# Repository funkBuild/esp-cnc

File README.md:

TODO
- position callback called on a timer. Motion handlers register with it for each axis
- Convert stepper to use position as mm instead of steps

- Brake outputs for each axis
- spindle speed variation. M138 / M139
  https://www.haascnc.com/service/codes-settings.type=mcode.machine=mill.value=M138.html

Haas - 
4th axis - M11 unclamp, M10 clamp
5th axis - M13 unclamp, M12 clamp

- Properly calculate feed rate on 3 axis (GRBL is wrong??)
- Calculate 5 axis feed rate using distance to axis of rotation
- Support inverse time feed rate

http://linuxcnc.org/docs/devel/html/motion/5-axis-kinematics.html
http://linuxcnc.org/docs/html/gcode/g-code.html#gcode:g93-g94-g95

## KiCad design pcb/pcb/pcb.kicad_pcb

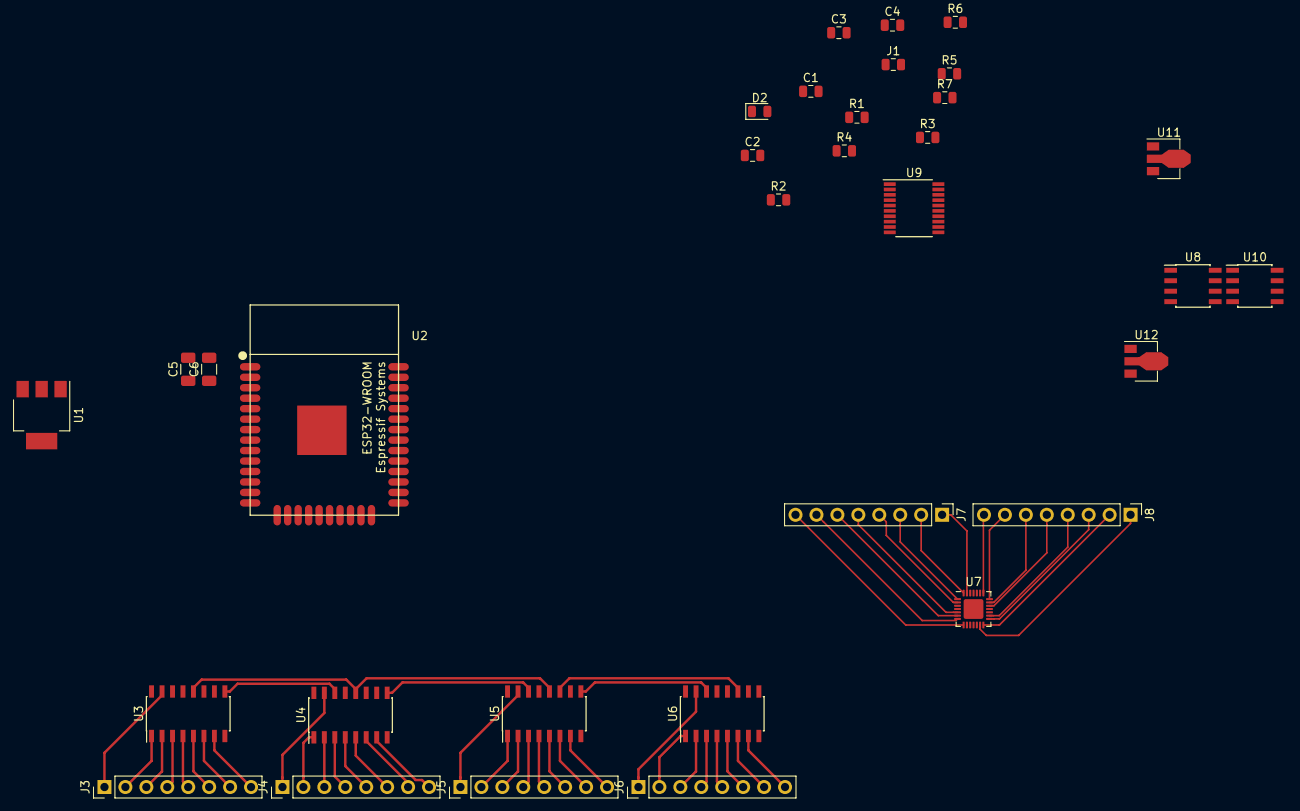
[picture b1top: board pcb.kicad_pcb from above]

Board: 2 copper layers, 33 parts (0 on the bottom side), 68 nets.

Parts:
C1, C4: C; C_0805_2012Metric
C2: 12nF; C_0805_2012Metric
C3: 10uF; C_0805_2012Metric
C5: 1uF/10V; C_1206_3216Metric
C6: 100uF/6.3v; C_1206_3216Metric
D2: D; D_0805_2012Metric
J1: Micro_SD_Card; R_0805_2012Metric
J3, J4, J5, J6, J7, J8: Conn_01x08_Male; PinHeader_1x08_P2.54mm_Vertical
R1: 5k; R_0805_2012Metric
R2: 12k; R_0805_2012Metric
R3, R4, R5, R6, R7: R; R_0805_2012Metric
U1: NCP1117-3.3_SOT223; SOT-223-3_TabPin2
U2: ESP32-WROOM
U3, U4, U5, U6: 74HC595; SOIC-16_3.9x9.9mm_P1.27mm
U7: SX1509B; QFN-28-1EP_4x4mm_P0.4mm_EP2.4x2.4mm
U8, U10: TL072; SOIC-8_3.9x4.9mm_P1.27mm
U9: PCM5102A; TSSOP-20_4.4x6.5mm_P0.65mm
U11: L78L12_SOT89; SOT-89-3
U12: L79L12_SOT89; SOT-89-3

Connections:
+3V3: C1.1, C4.1, C5.1, C6.1, R2.1, R3.1, R4.2, R5.1, R6.2, R7.1, U1.2, U2.2, U3.10, U3.16, U4.10, U4.16, U5.10, U5.16, U6.10, U6.16, U7.4, U7.12, U7.18, U9.1, U9.20
+12V: U8.8, U10.8, U11.1
+15V: C3.1, D2.1, R1.1, U1.3, U11.3
-12V: U8.4, U10.4, U12.3
/En: C2.1, R2.2, U2.3
/I2S Serial Expander/BCK: U3.11, U4.11, U5.11, U6.11
/I2S Serial Expander/D0: J3.1, U3.15
/I2S Serial Expander/D1: J3.2, U3.1
/I2S Serial Expander/D2: J3.3, U3.2
/I2S Serial Expander/D3: J3.4, U3.3
/I2S Serial Expander/D4: J3.5, U3.4
/I2S Serial Expander/D5: J3.6, U3.5
/I2S Serial Expander/D6: J3.7, U3.6
/I2S Serial Expander/D7: J3.8, U3.7
/I2S Serial Expander/D8: J4.1, U4.15
/I2S Serial Expander/D9: J4.2, U4.1
/I2S Serial Expander/D10: J4.3, U4.2
/I2S Serial Expander/D11: J4.4, U4.3
/I2S Serial Expander/D12: J4.5, U4.4
/I2S Serial Expander/D13: J4.6, U4.5
/I2S Serial Expander/D14: J4.7, U4.6
/I2S Serial Expander/D15: J4.8, U4.7
/I2S Serial Expander/D16: J5.1, U5.15
/I2S Serial Expander/D17: J5.2, U5.1
/I2S Serial Expander/D18: J5.3, U5.2
/I2S Serial Expander/D19: J5.4, U5.3
/I2S Serial Expander/D20: J5.5, U5.4
/I2S Serial Expander/D21: J5.6, U5.5
/I2S Serial Expander/D22: J5.7, U5.6
/I2S Serial Expander/D23: J5.8, U5.7
/I2S Serial Expander/D24: J6.1, U6.15
/I2S Serial Expander/D25: J6.2, U6.1
/I2S Serial Expander/D26: J6.3, U6.2
/I2S Serial Expander/D27: J6.4, U6.3
/I2S Serial Expander/D28: J6.5, U6.4
/I2S Serial Expander/D29: J6.6, U6.5
/I2S Serial Expander/D30: J6.7, U6.6
/I2S Serial Expander/D31: J6.8, U6.7
/I2S Serial Expander/WS: U3.12, U4.12, U5.12, U6.12
/INT: U2.12, U7.9
/IO19: U2.31, U9.14
/SCL: U2.11, U7.25
/SDA: U2.10, U7.24
/SD_CLK: R4.1, U2.13
/SD_CMD: R3.2, U2.23
/SD_DAT0: R6.1, U2.24
/SD_DAT2: J1.1, R7.2, U2.14
/SD_DAT3: J1.2, R5.2, U2.16
GND: C1.2, C2.2, C3.2, C4.2, C5.2, C6.2, U1.1, U2.1, U2.15, U2.38, U2.39, U3.8, U3.13, U4.8, U4.13, U5.8, U5.13, U6.8, U6.13, U7.3, U7.10, U7.17, U7.26, U9.3, U9.9, U9.10, U9.11, U9.16, U9.19, U10.3, U10.5, U11.2, U12.1
unnamed: J7.1, U7.27
unnamed: J7.2, U7.28
unnamed: J7.3, U7.1
unnamed: J7.4, U7.2
unnamed: J7.5, U7.5
unnamed: J7.6, U7.6
unnamed: J7.7, U7.7
unnamed: J7.8, U7.8
unnamed: J8.1, U7.13
unnamed: J8.2, U7.14
unnamed: J8.3, U7.15
unnamed: J8.4, U7.16
unnamed: J8.5, U7.19
unnamed: J8.6, U7.20
unnamed: J8.7, U7.21
unnamed: J8.8, U7.22
unnamed: U3.9, U4.14
unnamed: U4.9, U5.14
unnamed: U5.9, U6.14

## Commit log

2019-04-28 Remove archive
2020-12-16 Tidy up
2020-12-16 ESP IDF 4.x cmake support
